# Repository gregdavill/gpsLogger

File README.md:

# gpsLogger

MSP430F55xx based GPS logger, with USB MSC for log retrieval

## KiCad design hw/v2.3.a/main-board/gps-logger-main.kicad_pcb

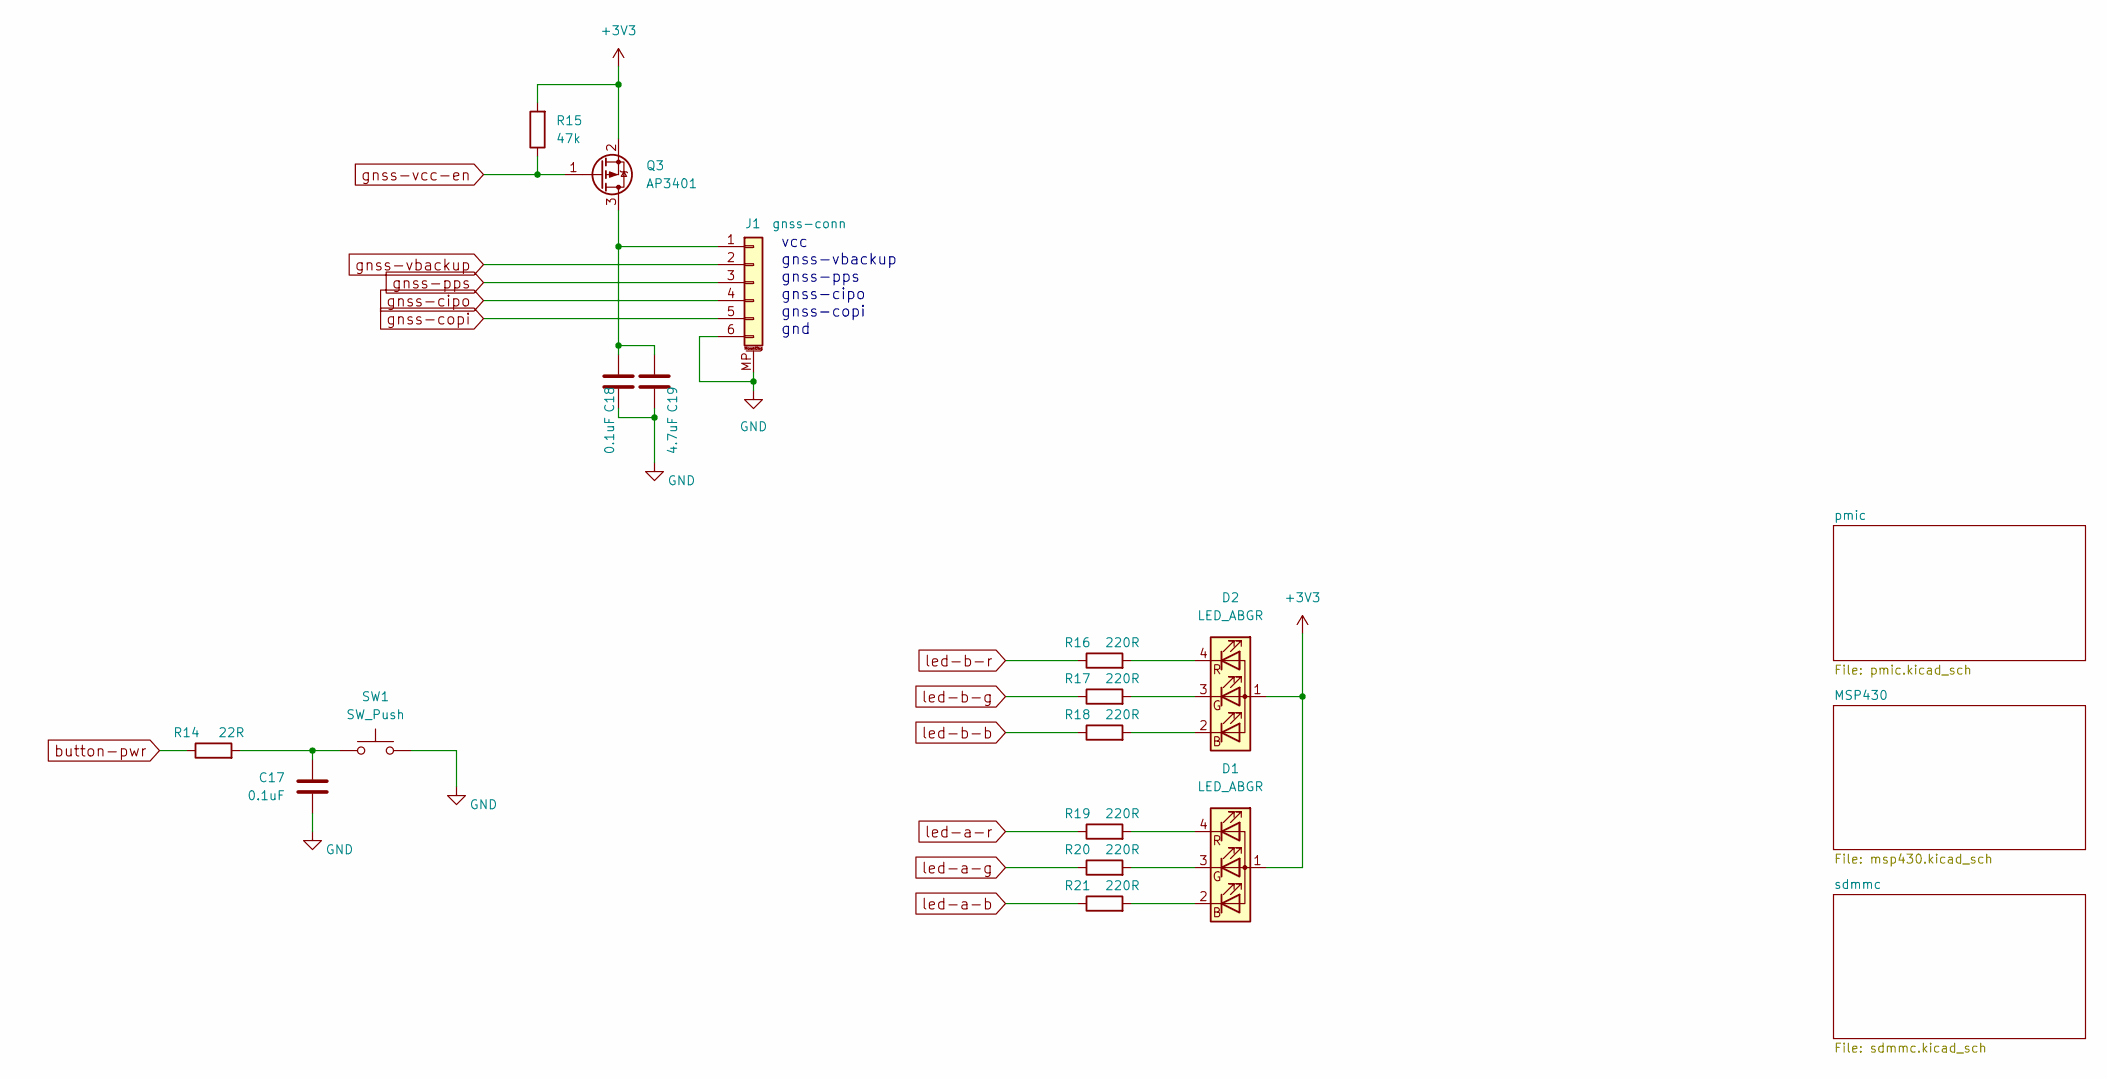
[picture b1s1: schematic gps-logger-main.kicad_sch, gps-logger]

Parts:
C17, C18: 0.1uF; C_0402_1005Metric
C19: 4.7uF; C_0402_1005Metric
D1, D2: LED_ABGR; 0404LED_RGB
J1: gnss-conn; Hirose_FH34SRJ-16S-0.5SH_1x16-1MP_P0.50mm_Horizontal
Q3: AP3401; SOT-23
R14: 22R; R_0402_1005Metric
R15: 47k; R_0402_1005Metric
R16, R17, R18, R19, R20, R21: 220R; R_0402_1005Metric
SW1: SW_Push; EVQ_switch

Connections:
+3V3: D1.1 (A), D2.1 (A), Q3.2 (S), R15.2; also elsewhere on the board
GND: C17.1, C18.1, C19.2, J1.6, J1.MP (MountPin), SW1.2; also elsewhere on the board
unnamed: C17.2, R14.2, SW1.1
unnamed: C18.2, C19.1, J1.1, Q3.3 (D)
unnamed: D1.2 (BK), R21.2
unnamed: D1.3 (GK), R20.2
unnamed: D1.4 (RK), R19.2
unnamed: D2.2 (BK), R18.2
unnamed: D2.3 (GK), R17.2
unnamed: D2.4 (RK), R16.2
button-pwr: R14.1; also elsewhere on the board
gnss-cipo: J1.4; also elsewhere on the board
gnss-copi: J1.5; also elsewhere on the board
gnss-pps: J1.3; also elsewhere on the board
gnss-vbackup: J1.2; also elsewhere on the board
gnss-vcc-en: Q3.1 (G), R15.1; also elsewhere on the board
led-a-b: R21.1; also elsewhere on the board
led-a-g: R20.1; also elsewhere on the board
led-a-r: R19.1; also elsewhere on the board
led-b-b: R18.1; also elsewhere on the board
led-b-g: R17.1; also elsewhere on the board
led-b-r: R16.1; also elsewhere on the board

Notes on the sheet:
vcc gnss-vbackup gnss-pps gnss-cipo gnss-copi gnd

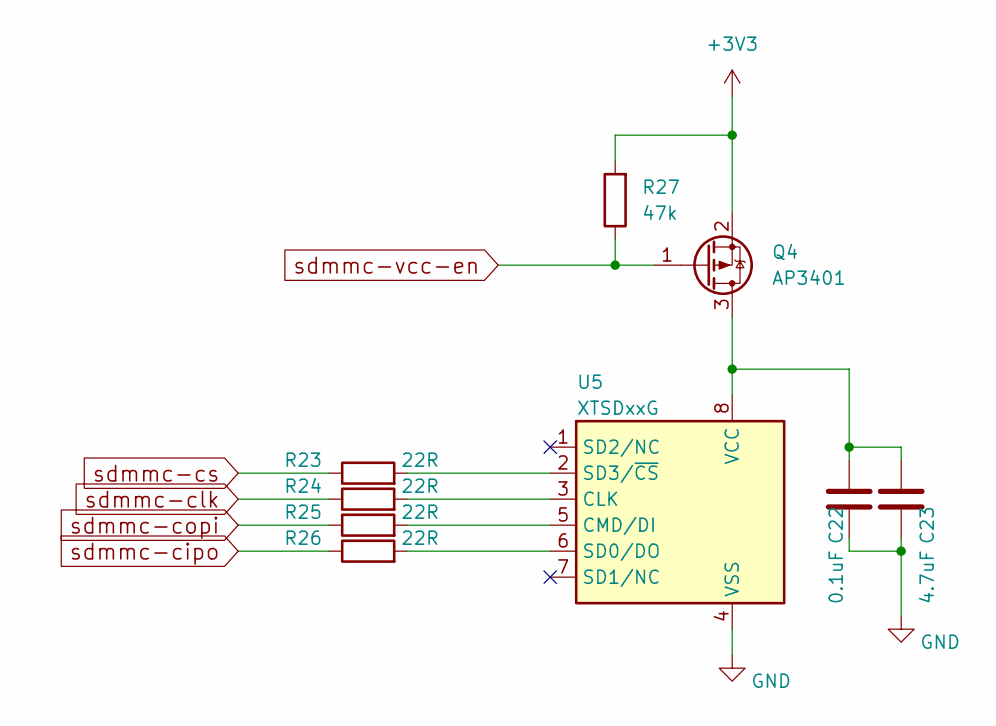
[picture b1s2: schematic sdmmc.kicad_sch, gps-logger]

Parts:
C22: 0.1uF; C_0402_1005Metric
C23: 4.7uF; C_0402_1005Metric
Q4: AP3401; SOT-23
R23, R24, R25, R26: 22R; R_0402_1005Metric
R27: 47k; R_0402_1005Metric
U5: XTSDxxG; LGA-8_8x6_Pitch1.27mm

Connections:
+3V3: Q4.2 (S), R27.2; also elsewhere on the board
GND: C22.1, C23.2, U5.4 (VSS); also elsewhere on the board
unnamed: C22.2, C23.1, Q4.3 (D), U5.8 (VCC)
unnamed: R23.2, U5.2 (SD3/~CS)
unnamed: R24.2, U5.3 (CLK)
unnamed: R25.2, U5.5 (CMD/DI)
unnamed: R26.2, U5.6 (SD0/DO)
sdmmc-cipo: R26.1; also elsewhere on the board
sdmmc-clk: R24.1; also elsewhere on the board
sdmmc-copi: R25.1; also elsewhere on the board
sdmmc-cs: R23.1; also elsewhere on the board
sdmmc-vcc-en: Q4.1 (G), R27.1; also elsewhere on the board

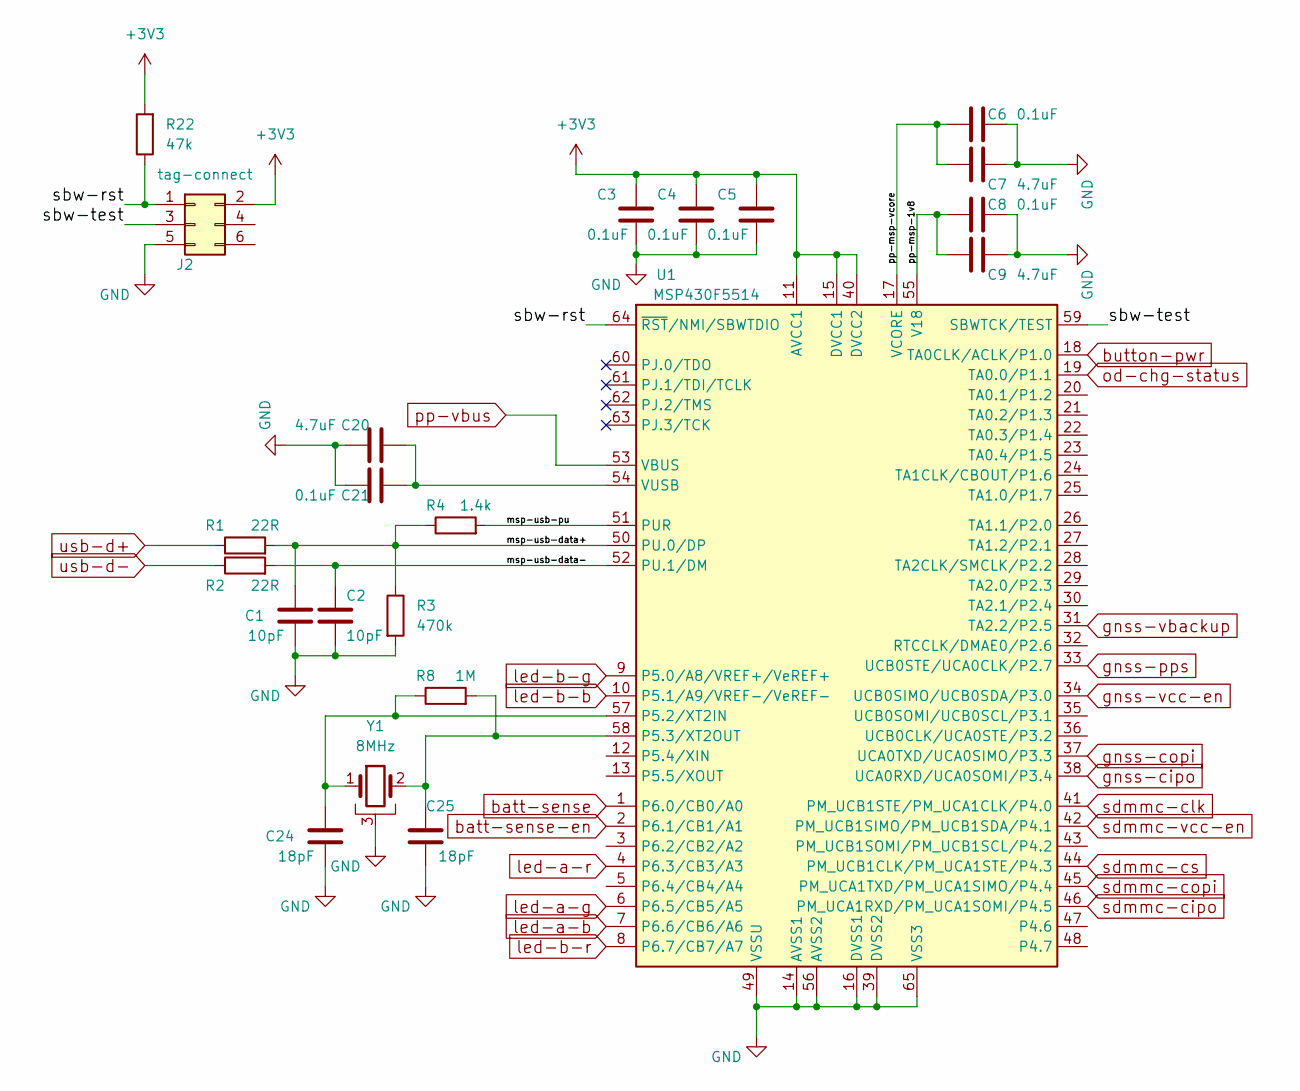
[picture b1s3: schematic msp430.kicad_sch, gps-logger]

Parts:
C1, C2: 10pF; C_0402_1005Metric
C3, C4, C5, C6, C8, C21: 0.1uF; C_0402_1005Metric
C7, C9, C20: 4.7uF; C_0402_1005Metric
C24, C25: 18pF; C_0402_1005Metric
J2: tag-connect; TC2030-NL_SMALL
R1, R2: 22R; R_0402_1005Metric
R3: 470k; R_0402_1005Metric
R4: 1.4k; R_0402_1005Metric
R8: 1M; R_0402_1005Metric
R22: 47k; R_0402_1005Metric
U1: MSP430F5514; QFN-64-1EP_9x9mm_P0.5mm_EP4.35x4.35mm
Y1: 8MHz; Crystal_SMD_Abracon_ABM8G-4Pin_3.2x2.5mm

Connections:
+3V3: C3.1, C4.1, C5.1, J2.2, R22.2, U1.11 (AVCC1), U1.15 (DVCC1), U1.40 (DVCC2); also elsewhere on the board
/MSP430/msp-usb-data+: C1.1, R1.2, R3.1, R4.1, U1.50 (PU.0/DP)
/MSP430/msp-usb-data-: C2.1, R2.2, U1.52 (PU.1/DM)
/MSP430/msp-usb-pu: R4.2, U1.51 (PUR)
/MSP430/pp-msp-1v8: C8.2, C9.1, U1.55 (V18)
/MSP430/pp-msp-vcore: C6.2, C7.1, U1.17 (VCORE)
/MSP430/sbw-rst: J2.1, R22.1, U1.64 (~RST/NMI/SBWTDIO)
/MSP430/sbw-test: J2.3, U1.59 (SBWTCK/TEST)
GND: C1.2, C2.2, C3.2, C4.2, C5.2, C6.1, C7.2, C8.1, C9.2, C20.2, C21.1, C24.2, C25.2, J2.5, R3.2, U1.14 (AVSS1), U1.16 (DVSS1), U1.39 (DVSS2), U1.49 (VSSU), U1.56 (AVSS2), U1.65 (VSS3), Y1.3; also elsewhere on the board
unnamed: C20.1, C21.2, U1.54 (VUSB)
unnamed: C24.1, R8.1, U1.57 (P5.2/XT2IN), Y1.1
unnamed: C25.1, R8.2, U1.58 (P5.3/XT2OUT), Y1.2
batt-sense: U1.1 (P6.0/CB0/A0); also elsewhere on the board
batt-sense-en: U1.2 (P6.1/CB1/A1); also elsewhere on the board
button-pwr: U1.18 (TA0CLK/ACLK/P1.0); also elsewhere on the board
gnss-cipo: U1.38 (UCA0RXD/UCA0SOMI/P3.4); also elsewhere on the board
gnss-copi: U1.37 (UCA0TXD/UCA0SIMO/P3.3); also elsewhere on the board
gnss-pps: U1.33 (UCB0STE/UCA0CLK/P2.7); also elsewhere on the board
gnss-vbackup: U1.31 (TA2.2/P2.5); also elsewhere on the board
gnss-vcc-en: U1.34 (UCB0SIMO/UCB0SDA/P3.0); also elsewhere on the board
led-a-b: U1.7 (P6.6/CB6/A6); also elsewhere on the board
led-a-g: U1.6 (P6.5/CB5/A5); also elsewhere on the board
led-a-r: U1.4 (P6.3/CB3/A3); also elsewhere on the board
led-b-b: U1.10 (P5.1/A9/VREF-/VeREF-); also elsewhere on the board
led-b-g: U1.9 (P5.0/A8/VREF+/VeREF+); also elsewhere on the board
led-b-r: U1.8 (P6.7/CB7/A7); also elsewhere on the board
od-chg-status: U1.19 (TA0.0/P1.1); also elsewhere on the board
pp-vbus: U1.53 (VBUS); also elsewhere on the board
sdmmc-cipo: U1.46 (PM_UCA1RXD/PM_UCA1SOMI/P4.5); also elsewhere on the board
sdmmc-clk: U1.41 (PM_UCB1STE/PM_UCA1CLK/P4.0); also elsewhere on the board
sdmmc-copi: U1.45 (PM_UCA1TXD/PM_UCA1SIMO/P4.4); also elsewhere on the board
sdmmc-cs: U1.44 (PM_UCB1CLK/PM_UCA1STE/P4.3); also elsewhere on the board
sdmmc-vcc-en: U1.42 (PM_UCB1SIMO/PM_UCB1SDA/P4.1); also elsewhere on the board
usb-d+: R1.1; also elsewhere on the board
usb-d-: R2.1; also elsewhere on the board

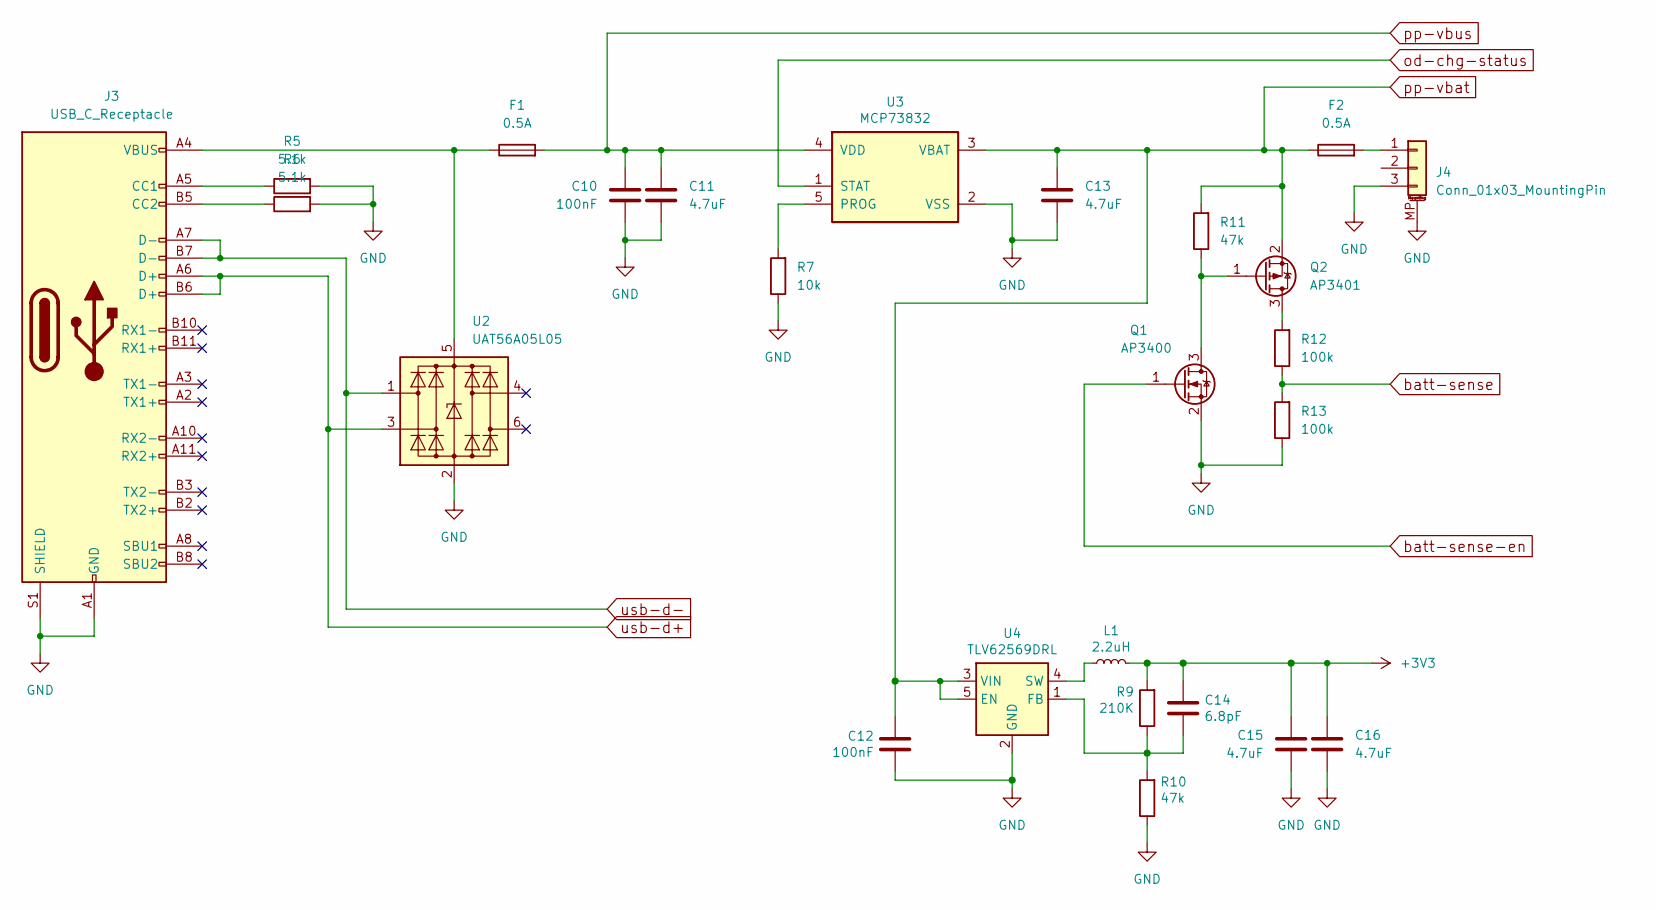
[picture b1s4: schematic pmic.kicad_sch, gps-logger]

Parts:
C10, C12: 100nF; C_0402_1005Metric
C11, C13, C15, C16: 4.7uF; C_0402_1005Metric
C14: 6.8pF; C_0402_1005Metric
F1, F2: 0.5A; Fuse_0402_1005Metric
J3: USB_C_Receptacle; usbc_vert_10132328
J4: Conn_01x03_MountingPin; JST_GH_SM03B-GHS-TB_1x03-1MP_P1.25mm_Horizontal
L1: 2.2uH; L_0805_2012Metric
Q1: AP3400; SOT-23
Q2: AP3401; SOT-23
R5, R6: 5.1k; R_0402_1005Metric
R7: 10k; R_0402_1005Metric
R9: 210K; R_0402_1005Metric
R10, R11: 47k; R_0402_1005Metric
R12, R13: 100k; R_0402_1005Metric
U2: UAT56A05L05; SOT-666
U3: MCP73832; SOT-23-5
U4: TLV62569DRL; SOT-666

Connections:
+3V3: C14.1, C15.1, C16.1, L1.2, R9.2; also elsewhere on the board
GND: C10.2, C11.2, C12.2, C13.2, C15.2, C16.2, J3.A1 (GND), J3.A12 (GND), J3.B1 (GND), J3.B12 (GND), J3.S1 (SHIELD), J4.3, J4.MP (MountPin), Q1.2 (S), R5.2, R6.2, R7.1, R10.1, R13.1, U2.2 (GND), U3.2 (VSS), U4.2 (GND); also elsewhere on the board
unnamed: C14.2, R9.1, R10.2, U4.1 (FB)
unnamed: F1.1, J3.A4 (VBUS), J3.A9 (VBUS), J3.B4 (VBUS), J3.B9 (VBUS), U2.5 (VBUS)
unnamed: F2.2, J4.1
unnamed: J3.A5 (CC1), R5.1
unnamed: J3.B5 (CC2), R6.1
unnamed: L1.1, U4.4 (SW)
unnamed: Q1.3 (D), Q2.1 (G), R11.1
unnamed: Q2.3 (D), R12.2
unnamed: R7.2, U3.5 (PROG)
batt-sense: R12.1, R13.2; also elsewhere on the board
batt-sense-en: Q1.1 (G); also elsewhere on the board
od-chg-status: U3.1 (STAT); also elsewhere on the board
pp-vbat: C12.1, C13.1, F2.1, Q2.2 (S), R11.2, U3.3 (VBAT), U4.3 (VIN), U4.5 (EN)
pp-vbus: C10.1, C11.1, F1.2, U3.4 (VDD); also elsewhere on the board
usb-d+: J3.A6 (D+), J3.B6 (D+), U2.3 (I/O2); also elsewhere on the board
usb-d-: J3.A7 (D-), J3.B7 (D-), U2.1 (I/O1); also elsewhere on the board

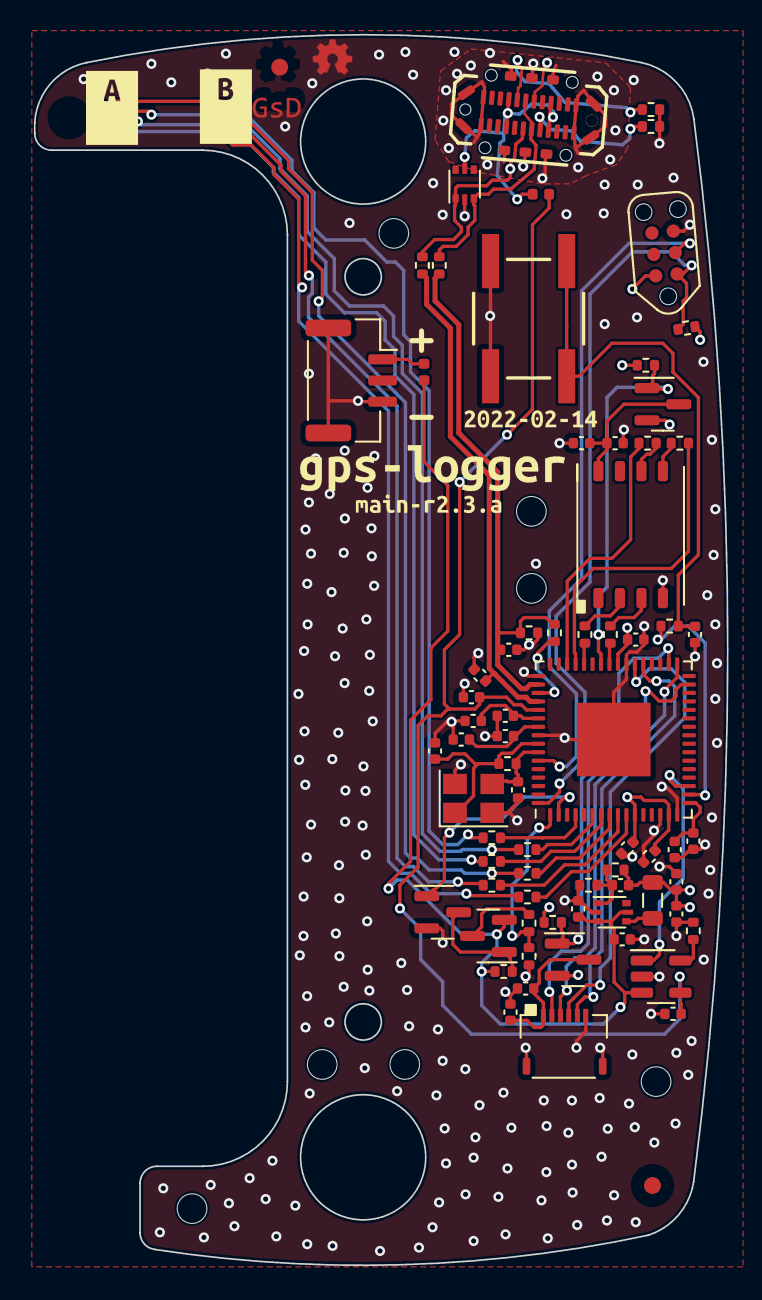
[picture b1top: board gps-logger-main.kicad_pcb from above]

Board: 4 copper layers, 40.9 x 72.7 mm, 77 parts (0 on the bottom side), 58 nets.

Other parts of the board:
kibuzzard-616D4B20: G***; kibuzzard-616D4B20
kibuzzard-6209DBB7: G***; kibuzzard-6209DBB7
kibuzzard-6209DBEB: G***; kibuzzard-6209DBEB
kibuzzard-6209DC67: G***; kibuzzard-6209DC67
kibuzzard-6209DC92: G***; kibuzzard-6209DC92

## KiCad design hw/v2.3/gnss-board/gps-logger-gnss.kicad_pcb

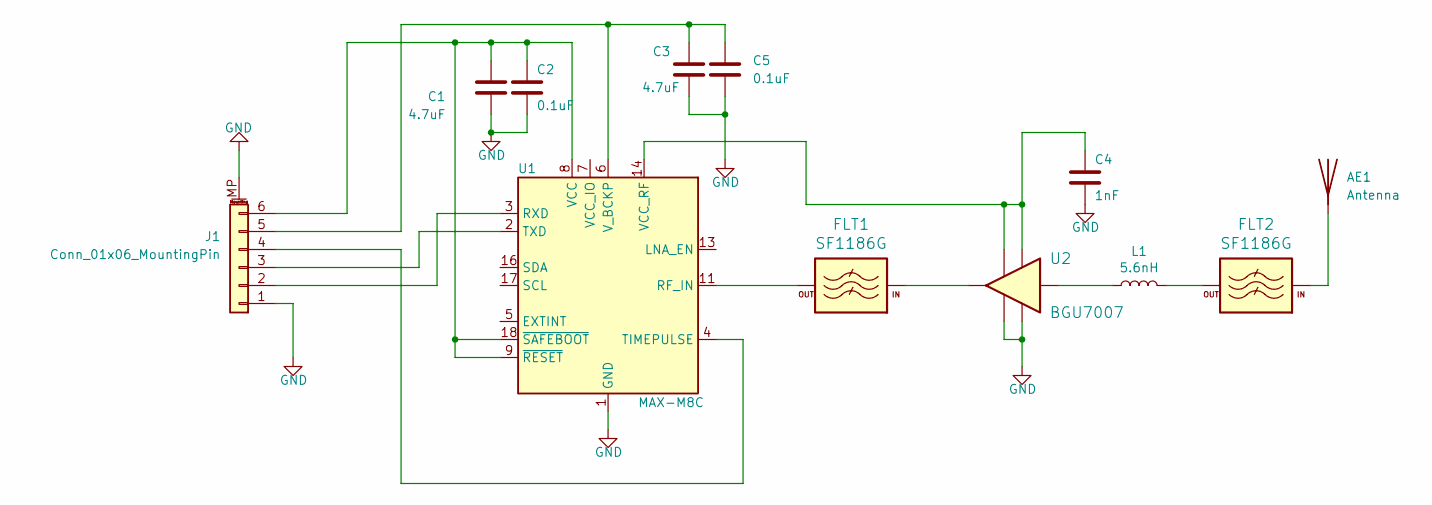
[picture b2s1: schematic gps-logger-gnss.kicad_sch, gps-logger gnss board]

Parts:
AE1: Antenna
C1, C3: 4.7uF; C_0402_1005Metric
C2, C5: 0.1uF; C_0402_1005Metric
C4: 1nF; C_0402
FLT1, FLT2: SF1186G; SAW-5
J1: Conn_01x06_MountingPin; Hirose_FH34SRJ-16S-0.5SH_1x16-1MP_P0.50mm_Horizontal
L1: 5.6nH; L_0402
U1: MAX-M8C; ublox_MAX
U2: BGU7007; XSON6

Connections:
GND: C1.2, C2.2, C3.2, C4.2, C5.2, FLT1.2, FLT1.4, FLT1.5, FLT2.2, FLT2.4, FLT2.5, J1.1, J1.MP (MountPin), U1.1 (GND), U1.10 (GND), U1.12 (GND), U2.4 (VCC), U2.5 (ENABLE)
unnamed 1: AE1.1, FLT2.1 (INPUT); also elsewhere on the board
unnamed: C1.1, C2.1, J1.6, U1.8 (VCC), U1.9 (~RESET), U1.18 (~SAFEBOOT)
unnamed: C3.1, C5.1, J1.5, U1.6 (V_BCKP)
unnamed: C4.1, U1.14 (VCC_RF), U2.1 (GND), U2.2 (GND)
unnamed: FLT1.1 (INPUT), U2.6 (RF_O)
unnamed: FLT1.3 (OUTPUT), U1.11 (RF_IN)
unnamed: FLT2.3 (OUTPUT), L1.2
unnamed: J1.2, U1.3 (RXD)
unnamed: J1.3, U1.2 (TXD)
unnamed: J1.4, U1.4 (TIMEPULSE)
unnamed: L1.1, U2.3 (RF_IN)

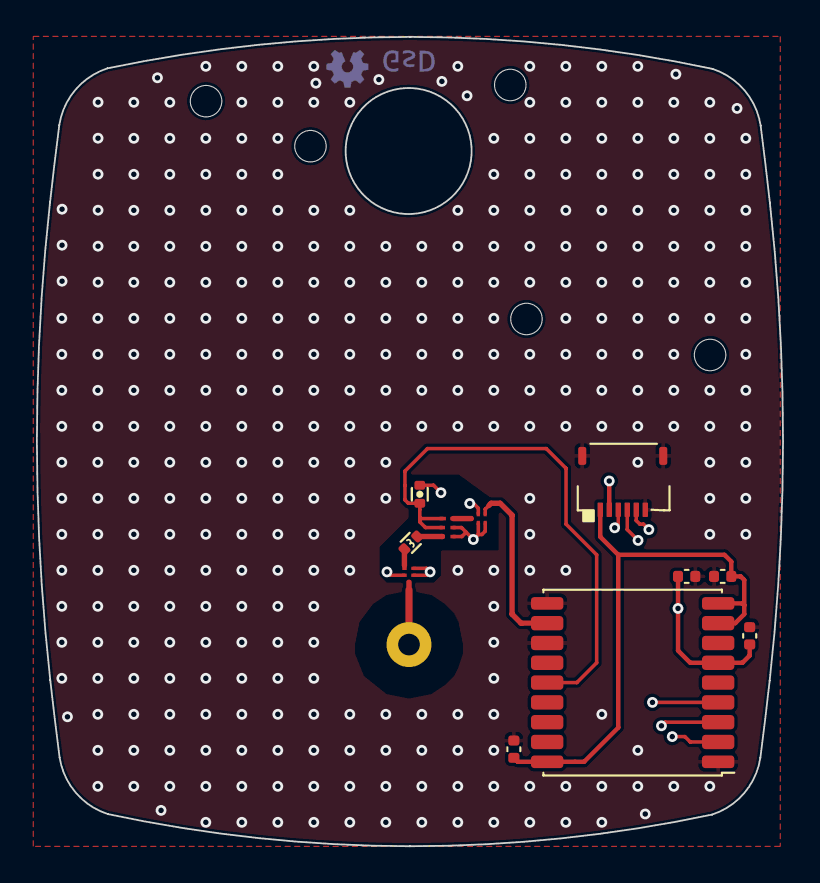
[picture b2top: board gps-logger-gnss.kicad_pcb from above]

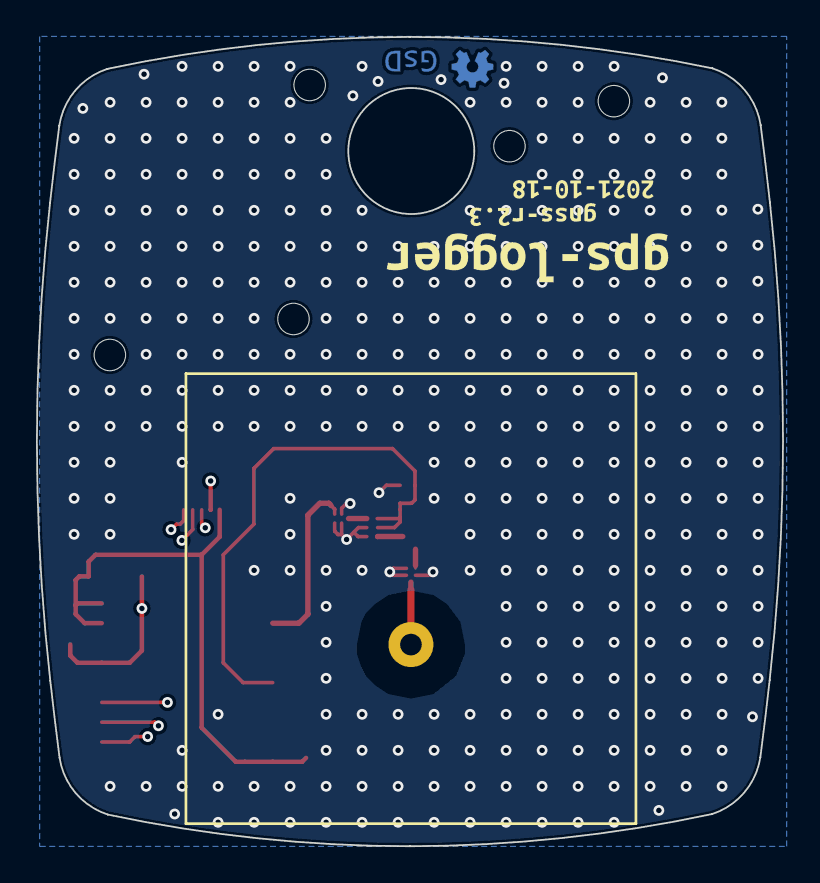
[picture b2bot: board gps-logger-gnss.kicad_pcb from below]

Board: 4 copper layers, 41.5 x 45.0 mm, 15 parts (4 on the bottom side), 12 nets.

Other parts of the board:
ANT1: pkl_PATCH_ANTENNA; GPS_ANT
kibuzzard-616D57EE: G***; kibuzzard-616D57EE
kibuzzard-616D5807: G***; kibuzzard-616D5807
kibuzzard-616D5817: G***; kibuzzard-616D5817

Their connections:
unnamed 1: ANT1.1; also elsewhere on the board

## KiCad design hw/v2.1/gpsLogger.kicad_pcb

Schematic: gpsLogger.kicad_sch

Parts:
ANT1: ANT; GPS_ANT
C1, C5, C7, C12: 10n; C_0603
C2, C3: 22p; C_0603
C4, C8, C13, C16, C17: 1uF; C_0603
C6, C9, C14, C15: C; C_0603
C10, C11, C18: 100n; C_0603
C19, C21, C22: 47pF; C_0603
C20: 1nF; C_0603
D1, D2: Led_RGB_CA; LITEON_RGB
FB1: 1k FB; R_0603
FLT1: B8813; SAW-5
IC1: MSP430F55xx; QFN-64-1EP_9x9mm_Pitch0.5mm
L1: 27nH; C_0603
L2, L3: 100nH; C_0603
L4: 5.6nH; C_0402
P1: USB_OTG; USB_VERT
P2: CONN_01X02; BM02B-GHS-TBT
Q2: FG6943010R; SC-70-6
R1, R2: 27R; R_0603
R3: 470k; R_0603
R4: 1k4; R_0603
R5, R8, R9, R11: 10k; R_0603
R6: 10R; R_0603
R7, R12, R13, R14, R15, R16, R17, R18, R19, R20, R21: R; R_0603
R10: 1k; R_0603
R22, R23, R24, R25, R26, R27, R28: 2k2; R_0603
SW1: SW_PUSH; EVQ_switch
TAG1: TAG_CONNECT; tag_connect
U1: MAX_M8Q; MAX_M8
U2: MCP73812; SOT-23-5
U3: uSD; SD_holder_472190001
U4, U5: MIC2091; SOT-23-5
U6: TPS78230; SOT-23-5
U7: BGU7007; XSON6
X1: CRYSTAL_SMD; CSTCR_G15C

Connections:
1v8: C16.1, IC1.55 (V18)
+3V3: C15.1, D1.1, D2.1, IC1.11 (AVCC), IC1.15 (DVCC), IC1.40 (DVCC), R9.2, R11.2, R15.1, TAG1.2 (VCC), U4.1 (IN), U5.1 (IN), U6.5 (OUT)
+BATT: C9.1, C14.1, P2.1, Q2.4 (D), R12.1, U2.3 (VBAT), U6.1 (IN), U6.3 (EN)
/ANT_RF: ANT1.1, C19.2
/LED_A_B: IC1.7 (P6.6), R18.2
/LED_A_G: IC1.6 (P6.5), R17.2
/LED_A_R: IC1.4 (P6.3), R16.2
/LED_B_B: IC1.10 (P5.1), R21.2
/LED_B_G: IC1.9 (P5.0), R20.2
/LED_B_R: IC1.8 (P6.7), R19.2
/OSC_IN: IC1.58 (P5.3/XT2OUT), X1.1
/OSC_OUT: IC1.57 (P5.2/XT2IN), X1.2
/PUR: IC1.51 (PUR), R4.1
/RST: IC1.64 (RST/SBWTDIO), R15.2, TAG1.1 (RESET/SBWTDIO)
/SENSE_EN: IC1.2 (P6.1), Q2.2 (G)
/TEST: IC1.59 (TEST/SBWTCK), TAG1.3 (TEST/SBWCLK)
/USB_DATA_N: C2.1, IC1.52 (PJ.2), R1.1
/USB_DATA_P: C3.1, IC1.50 (PU.0/DP), R2.1, R3.2, R4.2
/USB_IN_N: P1.2, R1.2
/USB_IN_P: P1.3, R2.2
/V_SENSE: IC1.1 (P6.0), R13.2, R14.1
GND: C1.2, C2.2, C3.2, C4.2, C5.2, C6.2, C7.2, C8.2, C9.2, C10.2, C11.2, C12.2, C13.2, C14.2, C15.2, C16.2, C17.2, C18.2, C20.2, FLT1.2, FLT1.3, FLT1.5, IC1.14 (AVSS), IC1.16 (DVSS), IC1.39 (DVSS), IC1.49 (VSSU), IC1.56 (AVSS), IC1.65, P1.5, P1.6, P2.2, Q2.1 (S), R3.1, R7.1, R14.2, SW1.2, TAG1.5 (GND), U1.1 (GND), U1.10 (GND), U1.12 (GND), U2.2 (VSS), U3.6 (VSS), U4.2 (GND), U5.2 (GND), U6.2 (GND), U6.4 (GND), U7.1 (GND), U7.2 (GND), X1.3
GPS_BACKUP: IC1.31 (P2.5), U1.6 (V_BCKP)
GPS_MISO: R26.2, U1.2 (TXD)
GPS_MOSI: R27.2, U1.3 (RXD)
GPS_PPS: R28.2, U1.4 (TIMEPULSE)
GPS_PWR: IC1.34 (P3.0), U4.3 (EN)
GPS_PWR_FAULT: IC1.35 (P3.1), R9.1, U4.4 (~FAULT)
GPS_RF_IN: C22.1, L1.2, U1.11 (RF_IN)
GPS_VCC: C10.1, C12.1, C13.1, L2.2, R5.2, R8.1, U1.7 (VCC_IO), U1.8 (VCC)
GPS_VCC_RF: C20.1, R6.1, U1.14 (VCC_RF), U7.4 (VCC), U7.5 (ENABLE)
MMC_CLK: R25.2, U3.5 (CLK)
MMC_CS: R24.2, U3.2 (CD)
MMC_MISO: R22.2, U3.7 (DAT0(MISO))
MMC_MOSI: R23.2, U3.3 (CMD(MOSI))
MMC_PWR: IC1.42 (P4.1), U5.3 (EN)
MMC_PWR_FAULT: IC1.43 (P4.2), R11.1, U5.4 (~FAULT)
MMC_VCC: C7.1, C8.1, C18.1, L3.2, U3.4 (VDD)
unnamed: C1.1, FB1.1, P1.1
unnamed: C4.1, IC1.17 (VCORE)
unnamed: C5.1, L1.1, R6.2
unnamed: C19.1, L4.1
unnamed: C21.1, FLT1.1 (INPUT)
unnamed: C21.2, U7.6 (RF_O)
unnamed: C22.2, FLT1.4 (OUTPUT)
unnamed: D1.2, R16.1
unnamed: D1.3, R17.1
unnamed: D1.4, R18.1
unnamed: D2.2, R19.1
unnamed: D2.3, R20.1
unnamed: D2.4, R21.1
unnamed: IC1.33 (P2.7), R28.1
unnamed: IC1.37 (P3.3), R27.1
unnamed: IC1.38 (P3.4), R26.1
unnamed: IC1.41 (P4.0), R25.1
unnamed: IC1.44 (P4.3), R24.1
unnamed: IC1.45 (P4.4), R23.1
unnamed: IC1.46 (P4.5), R22.1
unnamed: L2.1, U4.5 (VOUT)
unnamed: L3.1, U5.5 (VOUT)
unnamed: L4.2, U7.3 (RF_IN)
unnamed: Q2.3 (S), R13.1
unnamed: Q2.5 (G), Q2.6 (D), R12.2
unnamed: R5.1, U1.18 (SAFEBOOT_N)
unnamed: R7.2, U2.5 (PROG)
unnamed: R8.2, U1.9 (RESET_N)
unnamed: R10.2, SW1.1
PWR_BUT: C11.1, IC1.18 (P1.0), R10.1
VBUS: C6.1, FB1.2, IC1.53 (VBUS), U2.4 (VDD)
VUSB: C17.1, IC1.54 (VUSB)
~CHG: IC1.19 (P1.1), U2.1 (CE)

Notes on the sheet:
Possible parts: B39162B8813P810 AFS14A34-1588.66-T3

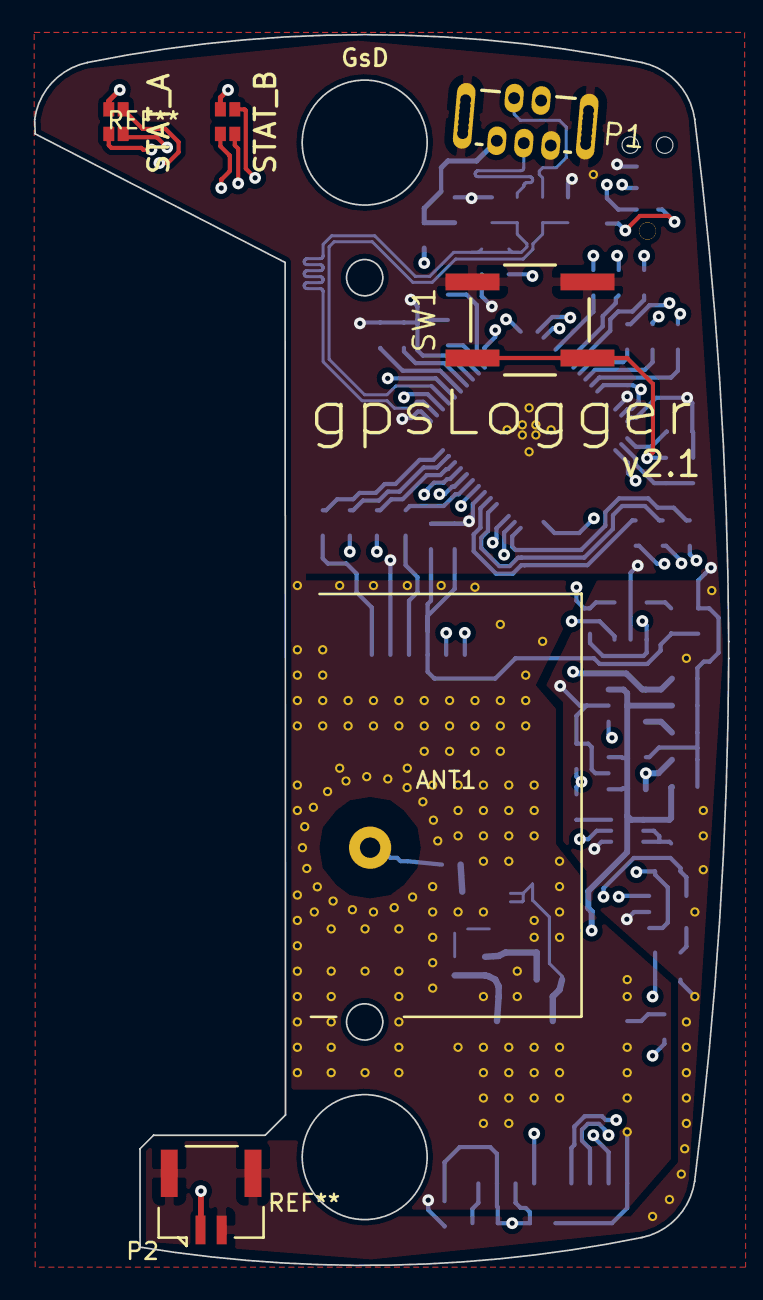
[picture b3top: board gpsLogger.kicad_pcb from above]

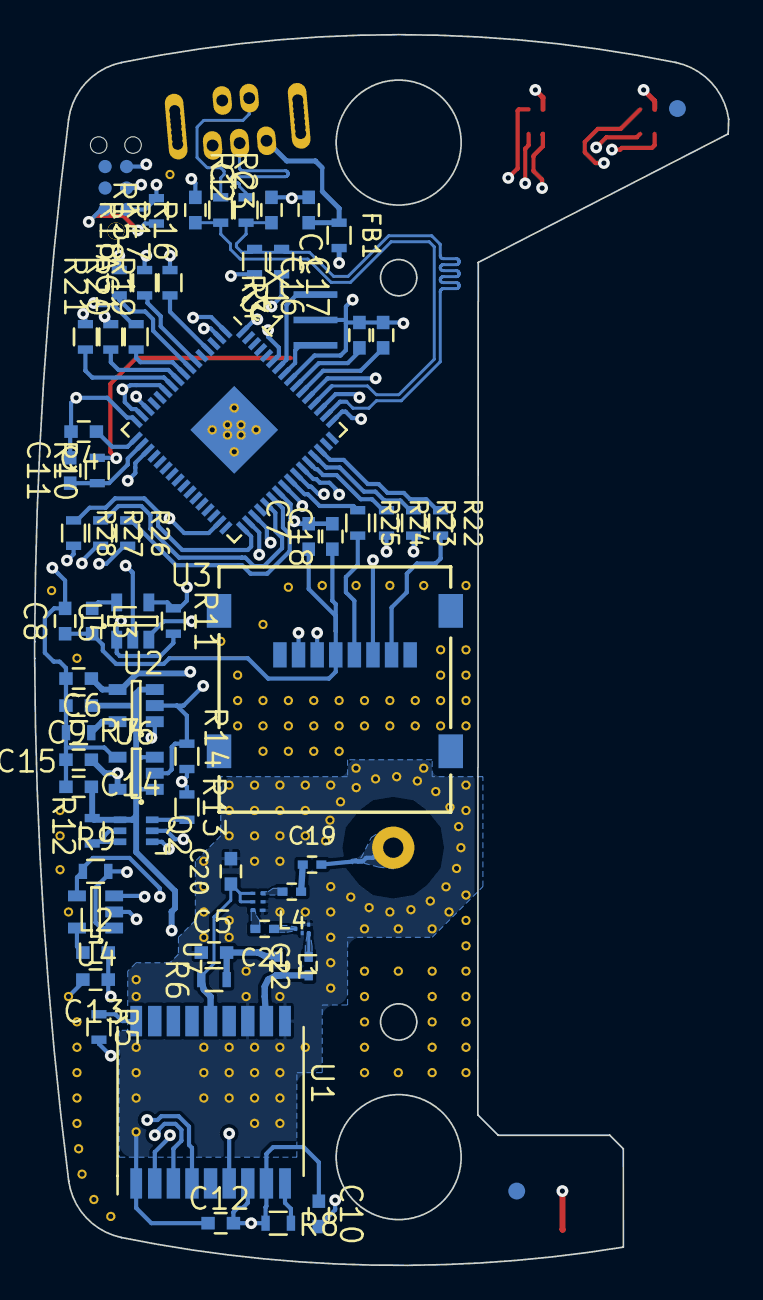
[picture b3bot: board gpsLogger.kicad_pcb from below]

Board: 4 copper layers, 41.0 x 72.8 mm, 73 parts (67 on the bottom side), 71 nets.

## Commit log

2016-01-09 Added initial fw files. Mostly from TI's M2 MSC USB example code.
2016-01-09 Added initial PCB files.
2016-01-10 Added some library parts, specific to this project
2016-01-16 Added USB vertical footprint. uSD card footprint. Did schematic, started rough PCB
2016-01-17 Added LED footprint, and Beagle GPS logo. Schematic done, PCB done.
2016-04-17 Created Gerbers
2016-04-17 Updated gpsLogger fw to newest version
2016-04-17 Removed Crude kml implementation
2016-04-17 Bug fix: Handle Safely remove / no host power supplies
2016-04-17 Added some simple NMEA GPS related functions
2016-04-17 Working NMEA to list of coords
2016-04-17 On board NMEA to KML working.
2016-04-17 Fixed LED blinking green, while turning off device
2016-04-17 moved KML from post, to realtime. Added simple FAT time from GPS time
2016-04-17 Moved raw logs into folder.
2016-04-17 FS_TINY = 1, remove extra buffer space from open files
2016-04-17 Corrected timestamp from GPS, increase NMEA ping-pong buffer size
2016-04-17 bug fix, buffer index overflow
2016-04-17 bug fix, LED stays green while GPS fix is active.
2016-04-17 bug fix, fix fattime parameters
2016-04-17 Added very basic timezone correction. Only adds fixed time of 9:30 for ACST time.
2016-04-17 moved timezone correction into gps_utils
2016-04-17 bug fix, fixup some stupid mistakes.
2016-04-17 Increase to NMEA update rate, now trialing at 5Hz
2016-04-22 Changed 5Hz to 2Hz. to stay within 9600baud bandwidth
2016-04-29 Minor changes, not effecting functionality
2016-06-28 Removed TI compiler build configuration
2016-06-28 Fixed .gitignore removing essential .lib files
2016-06-28 Add git commit to make process. Fix invald date printed on log files.
2016-06-28 Added git version tag into build. Pre-pending it into log files.
2016-06-28 Removed old stale code.
2016-06-28 Clear shared buffer before use.
2016-06-28 Added f_sync to gps_log file. Added case where two NMEA logs have the same name. (prepand dup with _1)
2016-06-28 Removed CRC check on incomming GPS data, bug found in the calculation
2016-06-28 Remove debug. Enable normal functionallity
2016-06-28 Halved SCLK speed to reduce SD failures.
2016-07-11 start new project structure using Mark3
2016-07-12 Add FatFs and driverlib
2016-07-13 add footprint for MAX M8Q GPS, Unroute PCB, Adjust schematic
2016-07-14 Added mic2091 power switch. Began routing PCB
2016-07-14 Finished Initial routing
2016-07-17 Finished routing
2016-07-17 Added PCB mount antenna and LNA + SAW filter. Re-routed PCB
2016-07-20 Added small link connecting ground pads.
2016-07-25 Added new footprints and basic BOM
2016-07-29 Added fabooh, USB libs and updated Fatfs calls.
2016-11-15 Updates to fw
2016-11-15 Updated main state machine for clarity.
2016-11-15 Updated GPS functions. Fixed error with duplicate files. Corrected GLONASS RMC capture
2017-02-11 Updates to ublox GPS handler, error checking, and first f_sync form powerup
2017-03-19 Updates to USART input. Now using a 256 byte FIFO. Much more reliable. Updates to NMEA logging. Now each sentence has it's checksum checked and then logged. KML file now has checks if it isn't create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
2017-06-16 Add Bootloader project
2017-06-17 Updated bootloader to use petitFatFs to save memory.
2017-06-17 'Merge' Hardware changes mistakely made on Mark3 branch
2017-06-18 Adde error output on LEDs and updated structure of program
2017-06-30 Clean up Bootloader project. Bootloader v0.1 release
2017-06-30 Update main firmware linker to include CRC value and fit within new App boundaries.
2017-07-01 Updated Firmware added file time to filename. Added compatibility layer to hal for LEDs based of GPS installed. Added code to reboot into bootloader when firmware found. added code to remove firmware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
2017-07-01 Removed delete of firmware file.
2017-07-01 Fix to bootloader flow to enable booting of app after error (No card/no File)
2017-07-29 Formatting changes. Fixed bug with date validity test, updates to initialisation of variables
2017-07-29 Added Timeout loop to SD card writes. Specifically for KML file.
2021-10-18 Move v2.1 hw into subfolder
2021-10-18 Add initial v2.3 hw
2021-10-18 Remove old files
2021-10-18 Update gitignore
2021-10-19 Update r2.3
    - Add make panel KiKit script
    - Add production gerbers
2021-10-19 Update PCBs to remove small vias
    - Regenerate 1x panel
    - Add gerbers
2021-12-01 Add GH Action
2021-12-01 Update GH Action
2022-01-30 Set up code to compile with MSP430-GCC/Makefile
2022-01-30 Adjust build steps
2022-02-07 Update workflow
2022-02-07 Update main-fw
2022-02-07 Add missing header
2022-02-07 Include ccs files
2022-02-07 Refactor projects
2022-02-07 Cleanup
2022-02-07 Add CRC to main file
    - Export binary output
2022-02-07 Add python crc to CI
2022-02-14 Update libs, USB enumerating
2022-02-14 Fix Bootloader -O setting
2022-02-14 Fix incorrect pin definition
2022-02-14 hw 2.3.a: New hw revision
    - Fix GNSS-cipo signal
    - Fix reversed pins to gnss connector
    - Update label with current date
    - Update version label
    - Change RGB LED labels
    - Generate gerbers
2022-02-14 hw 2.3.a: Add schematic
2022-08-19 ci: Add fw artifact to CI build
